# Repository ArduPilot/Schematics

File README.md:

# ArduPilot Hardware Archive

This is an archive of schematics for boards that ArduPilot supports. Note that ArduPilot supports many more boards than we
have schematics for here, but this archive covers some of the best known boards to help with ArduPilot development

Also note that pinouts for all boards supported by the ChibiOS port of ArduPilot usually can be found here:
  https://github.com/ArduPilot/ardupilot/tree/master/libraries/AP_HAL_ChibiOS/hwdef
  
Be sure to adhere to the license terms of the OEM providing the schematics. License terms are usually found in each
OEMs schematic folders. At a minimum, this usually requires attribution to the OEM and/or inclusion of the licensing language.

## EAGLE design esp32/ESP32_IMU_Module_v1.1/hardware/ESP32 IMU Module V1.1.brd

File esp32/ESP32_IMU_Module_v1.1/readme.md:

from: https://github.com/Makerfabs/ESP32_IMU_Module ( retrieved 4/4/2022)

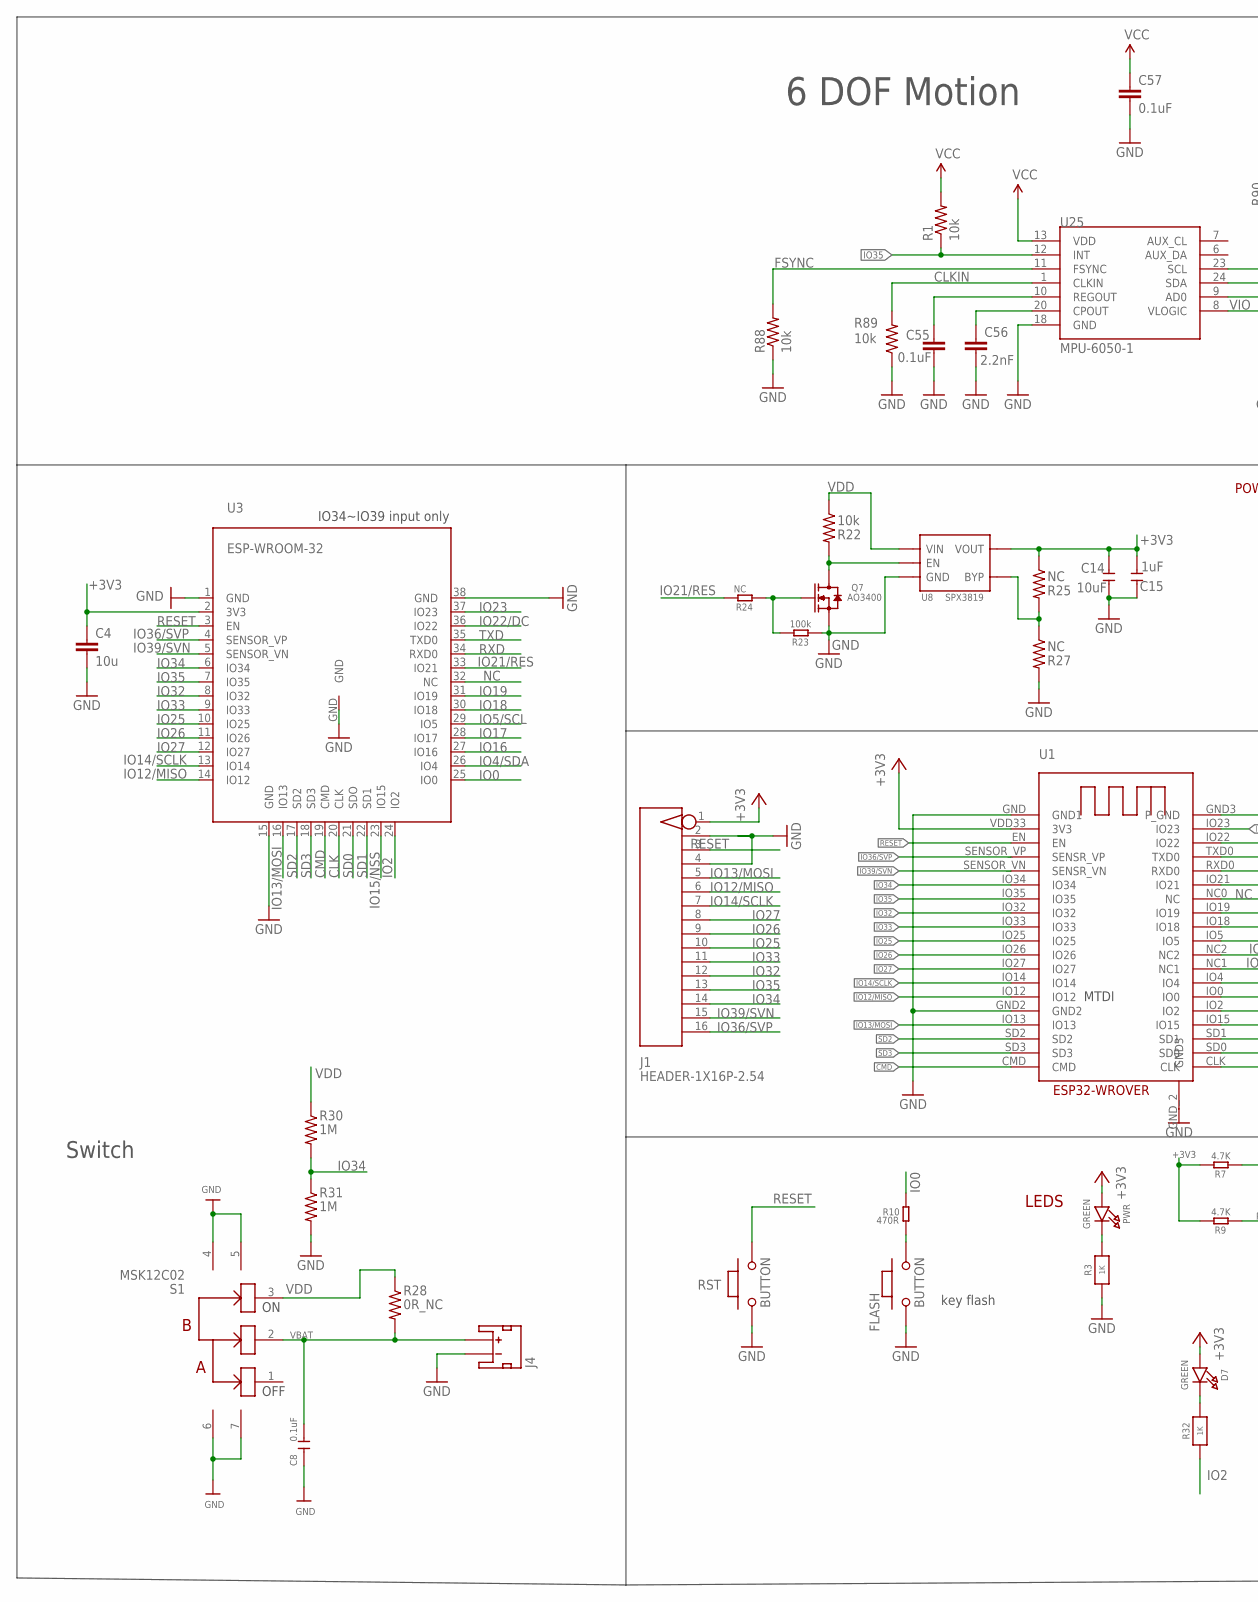
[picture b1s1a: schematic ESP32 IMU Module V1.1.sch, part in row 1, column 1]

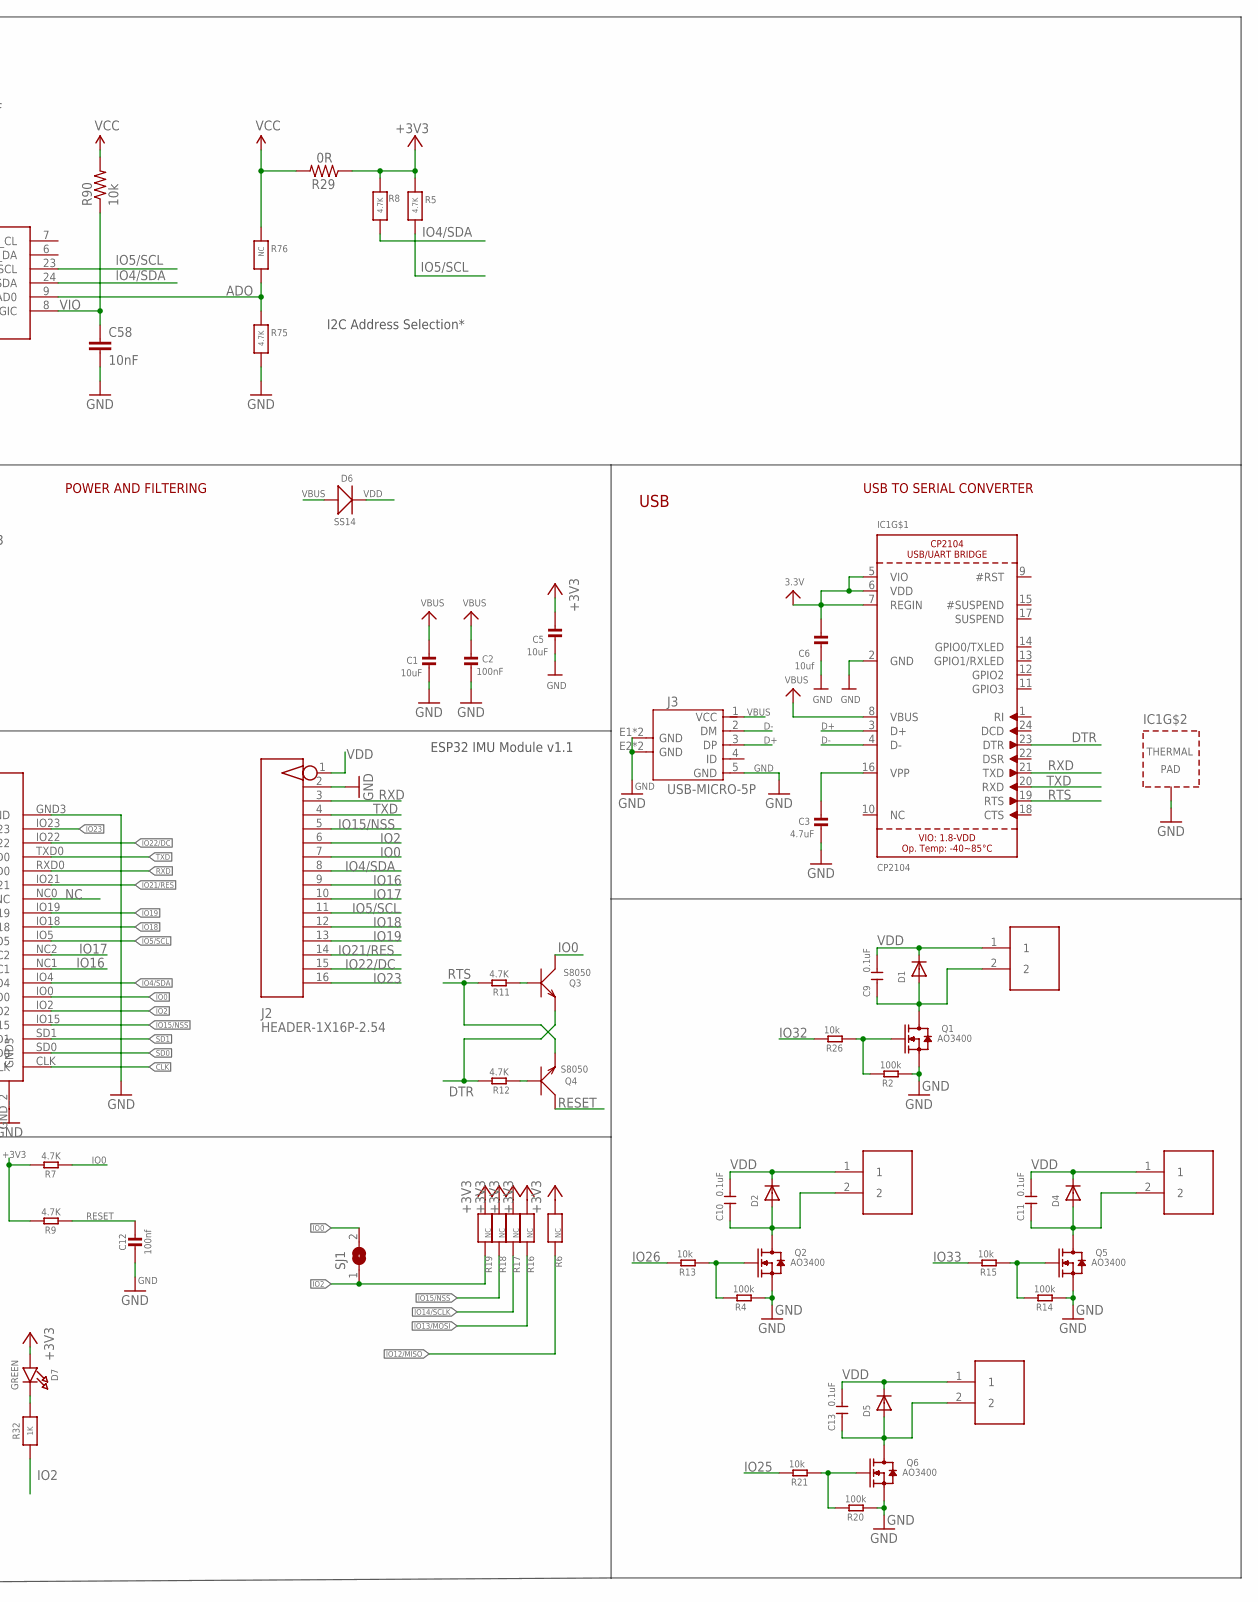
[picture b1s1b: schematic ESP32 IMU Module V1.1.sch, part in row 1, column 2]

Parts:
C1, C5: 10uF; 0603-NO
C2: 100nF; 0603-NO
C3: 4.7uF; 0603-NO
C4: 10u; C0603
C6: 10uf; 0603-NO
C8, C9, C10, C11, C13: 0.1uF; 0603
C12: 100nf; 0603-NO
C14: 10uF; 0603
C15: 1uF; 0603
C55, C57: 0.1uF; 0603-CAP
C56: 2.2nF; 0603-CAP
C58: 10nF; 0603-CAP
D1, D2, D4, D5: DIODESOD-323F; SOD-323F
D6: SS14; SOD323
D7: GREEN; CHIPLED_0805_NOOUTLINE
FLASH: BUTTON; 157SW
IC1: CP2104; QFN24_4MM_SMSC
J1, J2: HEADER-1X16P-2.54; DIP-1X16-2.54MM
J3: USB-MICRO-5P; MICRO-USB-5P
J4: JST_2MM_MALESMD; JST-2-SMD
M1, M2, M3, M4: PH2.0-2P-90-DIP
PWR: GREEN; CHIPLED_0805_NOOUTLINE
Q1, Q2, Q5, Q6, Q7: AO3400; SOT23@1
Q3, Q4: S8050; SOT23
R1, R22, R88, R89, R90: 10k; 0603-RES
R2, R4, R14, R20, R23: 100k; R0603
R3, R32: 1K; 0603-NO
R5, R8, R75: 4.7K; 0603-NO
R6, R16, R17, R18, R19, R76: NC; 0603-NO
R7, R9, R11, R12: 4.7K; R0603
R10: 470R; R0603
R13, R15, R21, R26: 10k; R0603
R24: NC; R0603
R25, R27: NC; 0603-RES
R28: 0R_NC; 0603-RES
R29: 0R; 0603-RES
R30, R31: 1M; 0603-RES
RST: BUTTON; 157SW
S1: MSK12C02; SMD7-6.6X2.7X2.5MM
SJ1: SJ
U1: ESP32-WROVER
U3: ESP-WROOM-32
U8: SPX3819; SOT23-5
U25: MPU-6050-1; QFN-24-4MM2

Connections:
+3V3: C4.1, C5.1, C6.1, C14.2, C15.2, D7.A, IC1.5 (VIO), IC1.6 (VDD), IC1.7 (REGIN), J1.1, PWR.A, R5.1, R6.1, R7.2, R8.1, R9.2, R16.1, R17.1, R18.1, R19.1, R25.1, R29.1, U1.VDD33 (3V3), U3.2 (3V3), U8.5 (VOUT)
ADO: R75.1, R76.2, U25.9 (AD0)
CLK: U1.CLK, U3.20 (CLK)
CLKIN: R89.2, U25.1 (CLKIN)
CMD: U1.CMD, U3.19 (CMD)
D+: IC1.3 (D+), J3.3 (DP)
D-: IC1.4 (D-), J3.2 (DM)
DTR: IC1.23 (DTR), Q3.2 (E), R12.2
FSYNC: R88.2, U25.11 (FSYNC)
GND: C1.2, C2.2, C3.2, C4.2, C5.2, C6.2, C8.1, C12.2, C14.1, C15.1, C55.2, C56.2, C57.2, C58.2, FLASH.1, IC1.2 (GND), IC1.THERM (TP), J1.2, J1.4, J2.2, J3.5 (GND), J3.E1 (GND), J3.E2 (GND), J3.P1 (GND), J3.P2 (GND), J4.1 (-), Q1.2 (S), Q2.2 (S), Q5.2 (S), Q6.2 (S), Q7.2 (S), R2.1, R3.1, R4.1, R14.1, R20.1, R23.1, R27.2, R31.2, R75.2, R88.1, R89.1, RST.1, S1.4, S1.5, S1.6, S1.7, U1.GND (GND1), U1.GND2, U1.GND3 (P_GND), U1.GND_2 (GND3), U3.1 (GND), U3.15 (GND), U3.38 (GND), U3.GND, U8.2 (GND), U25.18 (GND)
IO0: J2.7, Q3.3 (C), R7.1, R10.2, SJ1.2, U1.IO0, U3.25 (IO0)
IO2: J2.6, R19.2, R32.1, SJ1.1, U1.IO2, U3.24 (IO2)
IO4/SDA: J2.8, R8.2, U1.IO4, U3.26 (IO4), U25.24 (SDA)
IO5/SCL: J2.11, R5.2, U1.IO5, U3.29 (IO5), U25.23 (SCL)
IO12/MISO: J1.6, R6.2, U1.IO12, U3.14 (IO12)
IO13/MOSI: J1.5, R16.2, U1.IO13, U3.16 (IO13)
IO14/SCLK: J1.7, R17.2, U1.IO14, U3.13 (IO14)
IO15/NSS: J2.5, R18.2, U1.IO15, U3.23 (IO15)
IO16: J2.9, U1.NC1, U3.27 (IO16)
IO17: J2.10, U1.NC2, U3.28 (IO17)
IO18: J2.12, U1.IO18, U3.30 (IO18)
IO19: J2.13, U1.IO19, U3.31 (IO19)
IO21/RES: J2.14, R24.2, U1.IO21, U3.33 (IO21)
IO22/DC: J2.15, U1.IO22, U3.36 (IO22)
IO23: J2.16, U1.IO23, U3.37 (IO23)
IO25: J1.10, R21.2, U1.IO25, U3.10 (IO25)
IO26: J1.9, R13.2, U1.IO26, U3.11 (IO26)
IO27: J1.8, U1.IO27, U3.12 (IO27)
IO32: J1.12, R26.2, U1.IO32, U3.8 (IO32)
IO33: J1.11, R15.2, U1.IO33, U3.9 (IO33)
IO34: J1.14, R30.2, R31.1, U1.IO34, U3.6 (IO34)
IO35: J1.13, R1.1, U1.IO35, U3.7 (IO35), U25.12 (INT)
IO36/SVP: J1.16, U1.SENSOR_VP (SENSR_VP), U3.4 (SENSOR_VP)
IO39/SVN: J1.15, U1.SENSOR_VN (SENSR_VN), U3.5 (SENSOR_VN)
unnamed: C9.1, D1.A, M1.2, Q1.3 (D)
unnamed: Q2.1 (G), R4.2, R13.1
unnamed: C10.1, D2.A, M4.2, Q2.3 (D)
unnamed: Q1.1 (G), R2.2, R26.1
unnamed: PWR.C, R3.2
unnamed: Q5.1 (G), R14.2, R15.1
unnamed: C11.1, D4.A, M2.2, Q5.3 (D)
unnamed: Q6.1 (G), R20.2, R21.1
unnamed: C13.1, D5.A, M3.2, Q6.3 (D)
unnamed: Q7.3 (D), R22.2, U8.3 (EN)
unnamed: Q7.1 (G), R23.2, R24.1
unnamed: D7.C, R32.2
unnamed: Q4.1 (B), R12.1
unnamed: Q3.1 (B), R11.1
unnamed: FLASH.2, R10.1
unnamed: R25.2, R27.1, U8.4 (BYP)
unnamed: C56.1, U25.20 (CPOUT)
unnamed: C55.1, U25.10 (REGOUT)
NC: U1.NC0 (NC), U3.32 (NC)
RESET: C12.1, J1.3, Q4.3 (C), R9.1, RST.2, U1.EN, U3.3 (EN)
RTS: IC1.19 (RTS), Q4.2 (E), R11.2
RXD: IC1.21 (TXD), J2.3, U1.RXD0, U3.34 (RXD0)
SD0: U1.SD0, U3.21 (SDO)
SD1: U1.SD1, U3.22 (SD1)
SD2: U1.SD2, U3.17 (SD2)
SD3: U1.SD3, U3.18 (SD3)
TXD: IC1.20 (RXD), J2.4, U1.TXD0, U3.35 (TXD0)
VBAT: C8.2, J4.2 (+), R28.2, S1.2
VBUS: C1.1, C2.1, D6.+, IC1.8 (VBUS), J3.1 (VCC)
VBUS1: C3.1, IC1.16 (VPP)
VCC: C57.1, R1.2, R29.2, R76.1, R90.2, U25.13 (VDD)
VDD: C9.2, C10.2, C11.2, C13.2, D1.C, D2.C, D4.C, D5.C, D6.-, J2.1, M1.1, M2.1, M3.1, M4.1, R22.1, R28.1, R30.1, S1.3, U8.1 (VIN)
VIO: C58.1, R90.1, U25.8 (VLOGIC)

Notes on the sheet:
USB
LEDS
POWER AND FILTERING
USB TO SERIAL CONVERTER
key flash
ESP32 IMU Module v1.1
MTDI
IO34~IO39 input only
I2C Address Selection*
6 DOF Motion
OFF
Switch

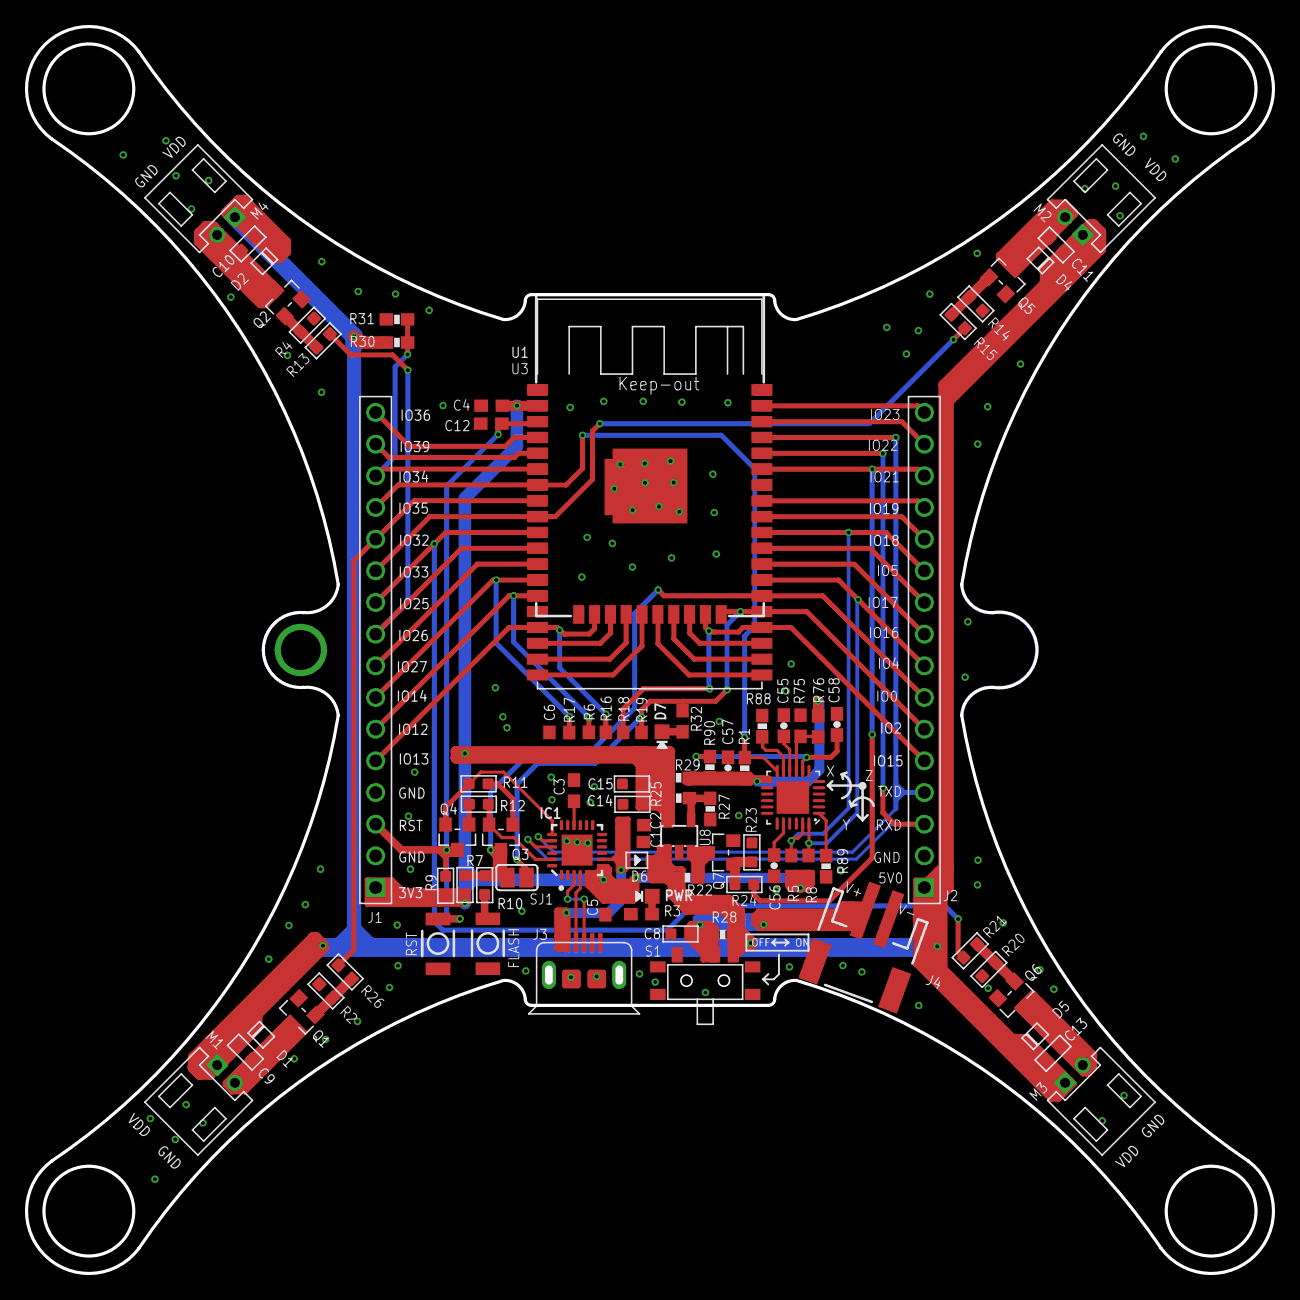
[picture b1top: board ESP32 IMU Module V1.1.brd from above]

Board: 2 copper layers, 100.0 x 100.0 mm, 87 parts (1 on the bottom side), 67 nets.

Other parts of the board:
U$1: MAKERFABS_0.3

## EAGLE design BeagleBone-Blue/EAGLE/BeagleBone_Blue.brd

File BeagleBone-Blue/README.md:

# BeagleBoard.org BeagleBone Blue
_BeagleBone optimized for robotics and machine control_

To optimize BeagleBone for education, BeagleBone Blue was created that integrates many components for robotics and machine control, including connectors for off-the-shelf robotic components. For education, this means you can quickly start talking about topics such as programming and control theory, without needing to spend so much time on electronics. The goal is to still be very hackable for learning electronics as well, including being fully open hardware.

BeagleBone Blue's legacy is primarily from contributions to BeagleBone Black robotics by [UCSD Flow Control and Coordinated Robotics Lab](http://robotics.ucsd.edu/), [Strawson Design](http://www.strawsondesign.com/), [Octavo Systems](http://octavosystems.com), [WowWee](http://www.wowwee.com/mip/), [National Instruments LabVIEW](http://www.ni.com/labview/) and of course the [BeagleBoard.org Foundation](https://beagleboard.org/about).

# Terms
These design materials are *NOT SUPPORTED* and *DO NOT* constitute a reference design. Only “community” support is allowed via resources at [BeagleBoard.org/discuss](https://beagleboard.org/discuss).

THERE IS NO WARRANTY FOR THE DESIGN MATERIALS, TO THE EXTENT PERMITTED BY APPLICABLE LAW. EXCEPT WHEN OTHERWISE STATED IN WRITING THE COPYRIGHT HOLDERS AND/OR OTHER PARTIES PROVIDE THE DESIGN MATERIALS “AS IS” WITHOUT WARRANTY OF ANY KIND, EITHER EXPRESSED OR IMPLIED, INCLUDING, BUT NOT LIMITED TO, THE IMPLIED WARRANTIES OF MERCHANTABILITY AND FITNESS FOR A PARTICULAR PURPOSE. THE ENTIRE RISK AS TO THE QUALITY AND PERFORMANCE OF THE DESIGN MATERIALS IS WITH YOU. SHOULD THE DESIGN MATERIALS PROVE DEFECTIVE, YOU ASSUME THE COST OF ALL NECESSARY SERVICING, REPAIR OR CORRECTION.

In other words, you may use the design materials as you choose and there is no license with regards to usage in the manufacturing process. We mean it, these design materials may be totally unsuitable for any purposes. Don't blame us!

As a general rule, we don't encourage use of this or other off-the-shelf single board computers in commercial products without engaging with a manufacturer to create a supplier agreement and make sure that you can get material as your business demands. Further, we do update the design on occasions where we find it necessary and won't guarantee a supply of older revisions, though we do seek periodic manufacturing of all of our boards for a period of roughly 10 years and will make design changes to replace obsolete parts and that may impact your usage. If you do opt to use it in a product, you take full responsibility for that product.

Do not use the BeagleBoard.org logo or trademarks (such as BeagleBoard and BeagleBone) on your products without a [logo license](https://beagleboard.org/logo) from the BeagleBoard.org Foundation, but feel free to reference BeagleBoard.org.

See the [LICENSE](https://github.com/beagleboard/beaglebone-blue/blob/master/LICENSE) file regarding the copyright of these materials.

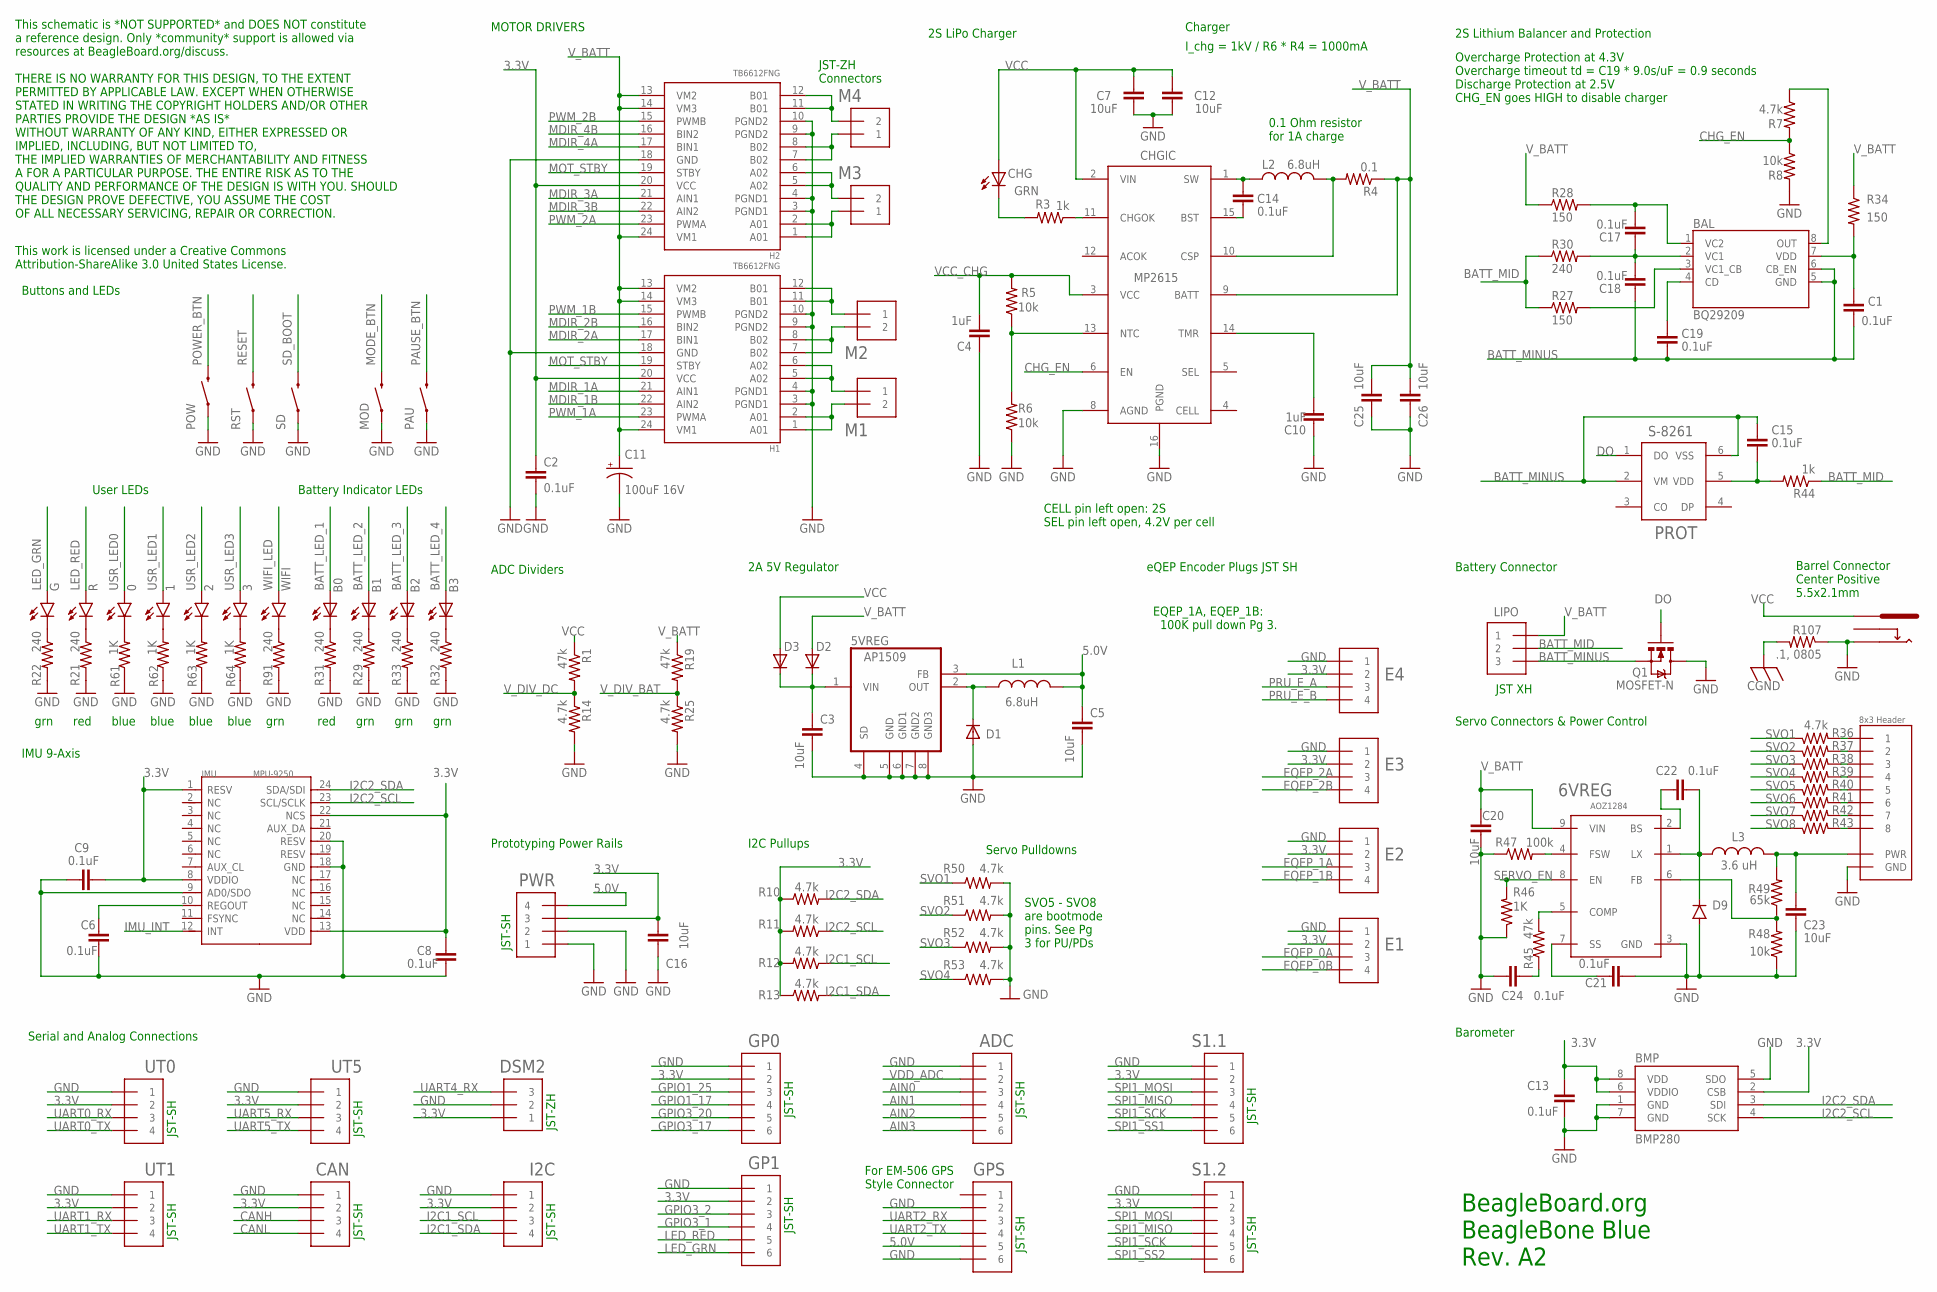
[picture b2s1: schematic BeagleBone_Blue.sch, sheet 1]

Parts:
0, 1, 2, 3: BLUE; BEAGLEBONE_BLUE_LED-0603
5VREG: AP1509SOIC-8-TIGHT; BEAGLEBONE_BLUE_SO08-TIGHT
6VREG: AOZ1284; SO08-EXPOSED
12V: PJ-102B_POWER_CON
ADC: JST_SH_6
B0: RED; LED-0603
B1, B2, B3: GREEN; LED-0603
BAL: BQ29209; 8-SON_3X3MM
BMP: BMP280
C1, C2, C6, C8, C9, C13, C14, C15, C17, C18, C19, C21, C22, C24: 0.1uF; 0402-CAP
C3, C5, C7, C12, C16, C20, C23, C25, C26: 10uF; 0805
C4, C10: 1uF; 0402-CAP
C11: 100uF 16V; PANASONIC_D
CAN: JST_SH_4; JST_SH_4_SMD
CHG: GRN; LED-0603
CHGIC: MP2615
D1, D2, D3: DIODE_SOD-123FL; ADAFRUIT_SOD-123FL
D9: DIODEDO214AA; DO-214AA
DSM2: JST_ZH_3
E1, E2, E3, E4: JST_SH_4; JST_SH_4_SMD
G: GREEN; BEAGLEBONE_BLUE_LED-0603
GP0, GP1: JST_SH_6
GPS: JST_SH_6
H1, H2: TB6612FNG; SSOP24
I2C: JST_SH_4; JST_SH_4_SMD
IMU: MPU-9250; QFN24G-0.4-3X3MM
J2: STRAWSON_EAGLE_LIB_SERVO_HEADERS_8X; STRAWSON_EAGLE_LIB_3X8_0.1"_HEADER
L1, L2: 6.8uH; SRN6045
L3: 3.6 uH; 8X8MM_INDUCTOR
LIPO: BATTERY; JST_XH_3-PIN
M1, M2, M3, M4: JST_ZH_2
MOD: SWITCH-MOMENTARY-2SMD-1101NE; TACTILE-SWITCH-1101NE
PAU: SWITCH-MOMENTARY-2SMD-1101NE; TACTILE-SWITCH-1101NE
POW: SWITCH-MOMENTARY-2SMD-1101NE; TACTILE-SWITCH-1101NE
PROT: S-8261; SOT-236
PWR: JST_SH_4; JST_SH_4_SMD
Q1: MOSFET-N; SO08-TIGHT
R: RED; BEAGLEBONE_BLUE_LED-0603
R1, R19, R45: 47k; 0402-RES
R3, R44: 1k; 0402-RES
R4: 0.1; 0603-RES
R5, R6, R8, R48: 10k; 0402-RES
R7, R10, R11, R12, R13, R14, R25, R36, R37, R38, R39, R40, R41, R42, R43, R50, R51, R52, R53: 4.7k; 0402-RES
R21, R22, R29, R30, R31, R32, R33, R91: 240; 0402-RES
R27, R28, R34: 150; 0402-RES
R46, R61, R62, R63, R64: 1K; 0402-RES
R47: 100k; 0402-RES
R49: 65k; 0402-RES
R107: .1, 0805; R0805
RST: SWITCH-MOMENTARY-2SMD-1101NE; TACTILE-SWITCH-1101NE
S1.1, S1.2: JST_SH_6
SD: SWITCH-MOMENTARY-2SMD-1101NE; TACTILE-SWITCH-1101NE
UT0, UT1, UT5: JST_SH_4; JST_SH_4_SMD
WIFI: GREEN; BEAGLEBONE_BLUE_LED-0603

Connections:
3.3V: BMP.2 (CSB), BMP.6 (VDDIO), BMP.8 (VDD), C2.2, C8.1, C9.2, C13.1, C16.1, CAN.2, DSM2.P$1 (1), E1.2, E2.2, E3.2, E4.2, GP0.2, GP1.2, H1.20 (VCC), H2.20 (VCC), I2C.2, IMU.1 (RESV), IMU.8 (VDDIO), IMU.13 (VDD), IMU.22 (NCS), PWR.3, R10.1, R11.2, R12.2, R13.1, S1.1.2, S1.2.2, UT0.2, UT1.2, UT5.2; also elsewhere on the board
5.0V: 5VREG.3 (FB), C5.1, GPS.5, L1.2, PWR.4; also elsewhere on the board
AIN0: ADC.3; also elsewhere on the board
AIN1: ADC.4; also elsewhere on the board
AIN2: ADC.5; also elsewhere on the board
AIN3: ADC.6; also elsewhere on the board
BATT_LED_1: B0.A; also elsewhere on the board
BATT_LED_2: B1.A; also elsewhere on the board
BATT_LED_3: B2.A; also elsewhere on the board
BATT_LED_4: B3.A; also elsewhere on the board
BATT_MID: LIPO.P$2 (2), R27.1, R30.1, R44.1
BATT_MINUS: BAL.5 (GND), BAL.6 (CB_EN), C1.2, C15.1, C18.1, C19.2, LIPO.P$3 (3), PROT.2 (VM), PROT.6 (VSS), Q1.1 (S), Q1.2 (S), Q1.3 (S)
CANH: CAN.3; also elsewhere on the board
CANL: CAN.4; also elsewhere on the board
CGND: R107.2; also elsewhere on the board
CHG_EN: CHGIC.6 (EN), R7.2, R8.1
CO: BAL.8 (OUT), R7.1
DO: PROT.1 (DO), Q1.4 (G)
EQEP_0A: E1.3; also elsewhere on the board
EQEP_0B: E1.4; also elsewhere on the board
EQEP_1A: E2.3; also elsewhere on the board
EQEP_1B: E2.4; also elsewhere on the board
EQEP_2A: E3.3; also elsewhere on the board
EQEP_2B: E3.4; also elsewhere on the board
GND: 5VREG.4 (SD), 5VREG.5 (GND), 5VREG.6 (GND1), 5VREG.7 (GND2), 5VREG.8 (GND3), 6VREG.3 (GND), 12V.OUT, ADC.1, BMP.1 (GND), BMP.5 (SDO), BMP.7 (GND), C2.1, C3.2, C4.1, C5.2, C6.2, C7.2, C8.2, C9.1, C10.1, C11.-, C12.2, C13.2, C16.2, C20.1, C21.1, C23.1, C24.1, C25.2, C26.2, CAN.1, CHGIC.8 (AGND), CHGIC.16 (PGND), D1.A, D9.A, DSM2.P$2 (2), E1.1, E2.1, E3.1, E4.1, GP0.1, GP1.1, GPS.2, GPS.6, H1.3 (PGND1), H1.4 (PGND1), H1.9 (PGND2), H1.10 (PGND2), H1.18 (GND), H2.3 (PGND1), H2.4 (PGND1), H2.9 (PGND2), H2.10 (PGND2), H2.18 (GND), I2C.1, IMU.9 (AD0/SDO), IMU.18 (GND), IMU.20 (RESV), J2.P$13 (GND), J2.P$14 (GND), J2.P$15 (GND), J2.P$16 (GND), J2.P$17 (GND), J2.P$18 (GND), J2.P$23 (GND), J2.P$24 (GND), MOD.1, PAU.1, POW.1, PWR.1, PWR.2, Q1.5 (D), Q1.6 (D), Q1.7 (D), Q1.8 (D), R6.1, R8.2, R14.2, R21.2, R22.2, R25.2, R29.2, R31.2, R32.2, R33.2, R46.1, R47.1, R48.1, R50.2, R51.2, R52.2, R53.2, R61.1, R62.1, R63.1, R64.1, R91.2, R107.1, RST.1, S1.1.1, S1.2.1, SD.1, UT0.1, UT1.1, UT5.1; also elsewhere on the board
GPIO1_17: GP0.4; also elsewhere on the board
GPIO1_25: GP0.3; also elsewhere on the board
GPIO3_1: GP1.4; also elsewhere on the board
GPIO3_2: GP1.3; also elsewhere on the board
GPIO3_17: GP0.6; also elsewhere on the board
GPIO3_20: GP0.5; also elsewhere on the board
I2C1_SCL: I2C.3, R12.1; also elsewhere on the board
I2C1_SDA: I2C.4, R13.2; also elsewhere on the board
I2C2_SCL: BMP.4 (SCK), IMU.23 (SCL/SCLK), R11.1; also elsewhere on the board
I2C2_SDA: BMP.3 (SDI), IMU.24 (SDA/SDI), R10.2; also elsewhere on the board
IMU_INT: IMU.12 (INT); also elsewhere on the board
L3: B2.C, R33.1
L4: B3.C, R32.1
LED_GRN: G.A, GP1.6; also elsewhere on the board
LED_RED: GP1.5, R.A; also elsewhere on the board
MDIR_1A: H1.21 (AIN1); also elsewhere on the board
MDIR_1B: H1.22 (AIN2); also elsewhere on the board
MDIR_2A: H1.17 (BIN1); also elsewhere on the board
MDIR_2B: H1.16 (BIN2); also elsewhere on the board
MDIR_3A: H2.21 (AIN1); also elsewhere on the board
MDIR_3B: H2.22 (AIN2); also elsewhere on the board
MDIR_4A: H2.17 (BIN1); also elsewhere on the board
MDIR_4B: H2.16 (BIN2); also elsewhere on the board
MODE_BTN: MOD.2; also elsewhere on the board
MOT1A: H1.1 (A01), H1.2 (A01), M1.P$2 (2)
MOT1B: H1.5 (A02), H1.6 (A02), M1.P$1 (1)
MOT2A: H1.11 (B01), H1.12 (B01), M2.P$1 (1)
MOT2B: H1.7 (B02), H1.8 (B02), M2.P$2 (2)
MOT3A: H2.1 (A01), H2.2 (A01), M3.P$1 (1)
MOT3B: H2.5 (A02), H2.6 (A02), M3.P$2 (2)
MOT4A: H2.11 (B01), H2.12 (B01), M4.P$2 (2)
MOT4B: H2.7 (B02), H2.8 (B02), M4.P$1 (1)
MOT_STBY: H1.19 (STBY), H2.19 (STBY); also elsewhere on the board
unnamed: J2.P$1 (1), R36.2
unnamed: G.C, R22.1
unnamed: BAL.2 (VC1), C17.1, C18.2, R30.2
unnamed: R.C, R21.1
unnamed: BAL.1 (VC2), C17.2, R28.2
unnamed: 6VREG.7 (SS), C21.2
unnamed: C15.2, PROT.5 (VDD), R44.2
unnamed: C6.1, IMU.10 (REGOUT)
unnamed: C14.1, CHGIC.15 (BST)
unnamed: 5VREG.2 (OUT), D1.C, L1.1
unnamed: CHG.C, R3.2
unnamed: CHGIC.11 (CHGOK), R3.1
unnamed: R91.1, WIFI.C
unnamed: BAL.4 (CD), C19.1
unnamed: J2.P$2 (2), R37.2
unnamed: BAL.7 (VDD), C1.1, R34.2
unnamed: J2.P$3 (3), R38.2
unnamed: J2.P$4 (4), R39.2
unnamed: 0.C, R61.2
unnamed: B1.C, R29.1
unnamed: B0.C, R31.1
unnamed: BAL.3 (VC1_CB), R27.2
unnamed: J2.P$5 (5), R40.2
unnamed: J2.P$6 (6), R41.2
unnamed: 6VREG.2 (BS), C22.1
unnamed: J2.P$19 (7), R42.2
unnamed: C14.2, CHGIC.1 (SW), L2.1
unnamed: J2.P$20 (8), R43.2
unnamed: 1.C, R62.2
unnamed: 2.C, R63.2
unnamed: 3.C, R64.2
unnamed: 6VREG.1 (LX), C22.2, D9.C, L3.1
unnamed: 6VREG.4 (FSW), R47.2
unnamed: C23.2, J2.P$7 (PWR), J2.P$8 (PWR), J2.P$9 (PWR), J2.P$10 (PWR), J2.P$11 (PWR), J2.P$12 (PWR), J2.P$21 (PWR), J2.P$22 (PWR), L3.2, R49.2
unnamed: 6VREG.5 (COMP), R45.2
unnamed: 6VREG.6 (FB), R48.2, R49.1
unnamed: C24.2, R45.1
unnamed: CHGIC.10 (CSP), L2.2, R4.2
unnamed: C10.2, CHGIC.14 (TMR)
unnamed: CHGIC.13 (NTC), R5.1, R6.2
unnamed: 5VREG.1 (VIN), C3.1, D2.C, D3.C
PAUSE_BTN: PAU.2; also elsewhere on the board
POWER_BTN: POW.2; also elsewhere on the board
PRU_E_A: E4.3; also elsewhere on the board
PRU_E_B: E4.4; also elsewhere on the board
PWM_1A: H1.23 (PWMA); also elsewhere on the board
PWM_1B: H1.15 (PWMB); also elsewhere on the board
PWM_2A: H2.23 (PWMA); also elsewhere on the board
PWM_2B: H2.15 (PWMB); also elsewhere on the board
RESET: RST.2; also elsewhere on the board
SD_BOOT: SD.2; also elsewhere on the board
SERVO_EN: 6VREG.8 (EN), R46.2; also elsewhere on the board
SPI1_MISO: S1.1.4, S1.2.4; also elsewhere on the board
SPI1_MOSI: S1.1.3, S1.2.3; also elsewhere on the board
SPI1_SCK: S1.1.5, S1.2.5; also elsewhere on the board
SPI1_SS1: S1.1.6; also elsewhere on the board
SPI1_SS2: S1.2.6; also elsewhere on the board
SVO1: R36.1, R50.1; also elsewhere on the board
SVO2: R37.1, R51.1; also elsewhere on the board
SVO3: R38.1, R52.1; also elsewhere on the board
SVO4: R39.1, R53.1; also elsewhere on the board
SVO5: R40.1; also elsewhere on the board
SVO6: R41.1; also elsewhere on the board
SVO7: R42.1; also elsewhere on the board
SVO8: R43.1; also elsewhere on the board
UART0_RX: UT0.3; also elsewhere on the board
UART0_TX: UT0.4; also elsewhere on the board
UART1_RX: UT1.3; also elsewhere on the board
UART1_TX: UT1.4; also elsewhere on the board
UART2_RX: GPS.3; also elsewhere on the board
UART2_TX: GPS.4; also elsewhere on the board
UART4_RX: DSM2.P$3 (3); also elsewhere on the board
UART5_RX: UT5.3; also elsewhere on the board
UART5_TX: UT5.4; also elsewhere on the board
USR_LED0: 0.A; also elsewhere on the board
USR_LED1: 1.A; also elsewhere on the board
USR_LED2: 2.A; also elsewhere on the board
USR_LED3: 3.A; also elsewhere on the board
VCC: 12V.IN, C7.1, C12.1, CHG.A, CHGIC.2 (VIN), D3.A, R1.1
VCC_CHG: C4.2, CHGIC.3 (VCC), R5.2
VDD_ADC: ADC.2; also elsewhere on the board
V_BATT: 6VREG.9 (VIN), C11.+, C20.2, C25.1, C26.1, CHGIC.9 (BATT), D2.A, H1.13 (VM2), H1.14 (VM3), H1.24 (VM1), H2.13 (VM2), H2.14 (VM3), H2.24 (VM1), LIPO.P$1 (1), R4.1, R19.1, R28.1, R34.1
V_DIV_BAT: R19.2, R25.1; also elsewhere on the board
V_DIV_DC: R1.2, R14.1; also elsewhere on the board
WIFI_LED: WIFI.A; also elsewhere on the board

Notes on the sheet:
BeagleBoard.org BeagleBone Blue Rev. A2
Barrel Connector Center Positive 5.5x2.1mm
ADC Dividers
Prototyping Power Rails
Buttons and LEDs
eQEP Encoder Plugs JST SH
I2C Pullups
2A 5V Regulator
Overcharge Protection at 4.3V Overcharge timeout td = C19 * 9.0s/uF = 0.9 seconds Discharge Protection at 2.5V CHG_EN goes HIGH to disable charger
I_chg = 1kV / R6 * R4 = 1000mA
Battery Indicator LEDs
MOTOR DRIVERS
Servo Connectors & Power Control
JST-ZH
Barometer
Charger
JST-ZH Connectors
IMU 9-Axis
For EM-506 GPS Style Connector
2S Lithium Balancer and Protection
red
grn
JST XH
Battery Connector
JST-SH
Serial and Analog Connections
Servo Pulldowns
2S LiPo Charger
0.1 Ohm resistor for 1A charge
CELL pin left open: 2S SEL pin left open, 4.2V per cell
This schematic is *NOT SUPPORTED* and DOES NOT constitute a reference design. Only *community* support is allowed via resources at BeagleBoard.org/discuss. THERE IS NO WARRANTY FOR THIS DESIGN, TO THE EXTENT PERMITTED BY APPLICABLE LAW. EXCEPT WHEN OTHERWISE STATED IN WRITING THE COPYRIGHT HOLDERS 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
This work is licensed under a Creative Commons Attribution-ShareAlike 3.0 United States License.
User LEDs
blue
EQEP_1A, EQEP_1B: 100K pull down Pg 3.
SVO5 - SVO8 are bootmode pins. See Pg 3 for PU/PDs

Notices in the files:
parts and their libraries:
SparkFun-Electromechanical: Licensing: CC v3.0 Share-Alike You are welcome to use this library for commercial purposes.
microbuilder: This work is placed in the public domain, and may be freely used for commercial and non-commercial work with the following conditions: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
